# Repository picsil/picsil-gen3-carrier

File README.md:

# picsil-gen3-carrier
A carrier board for Particle Boron with support for three OneWire or dry contact sensors, onboard 32KB FRAM and DS18B20 temperature sensor, and ESD protected sensor inputs.

## NOTE
There are known problems with this circuit. Be aware of this before using it, since you will need to make changes.

### Known issues:
- J1-J3 use the wrong footprint. It uses STX-3120-3BM (mono), where it should be STX-3120-3B (stereo).
- U4 uses the wrong footprint, at least for the parts I have. I was unable to find a part that uses the footprint in this design.
- D4 is potentially a problem. Consider removing it if unsure.

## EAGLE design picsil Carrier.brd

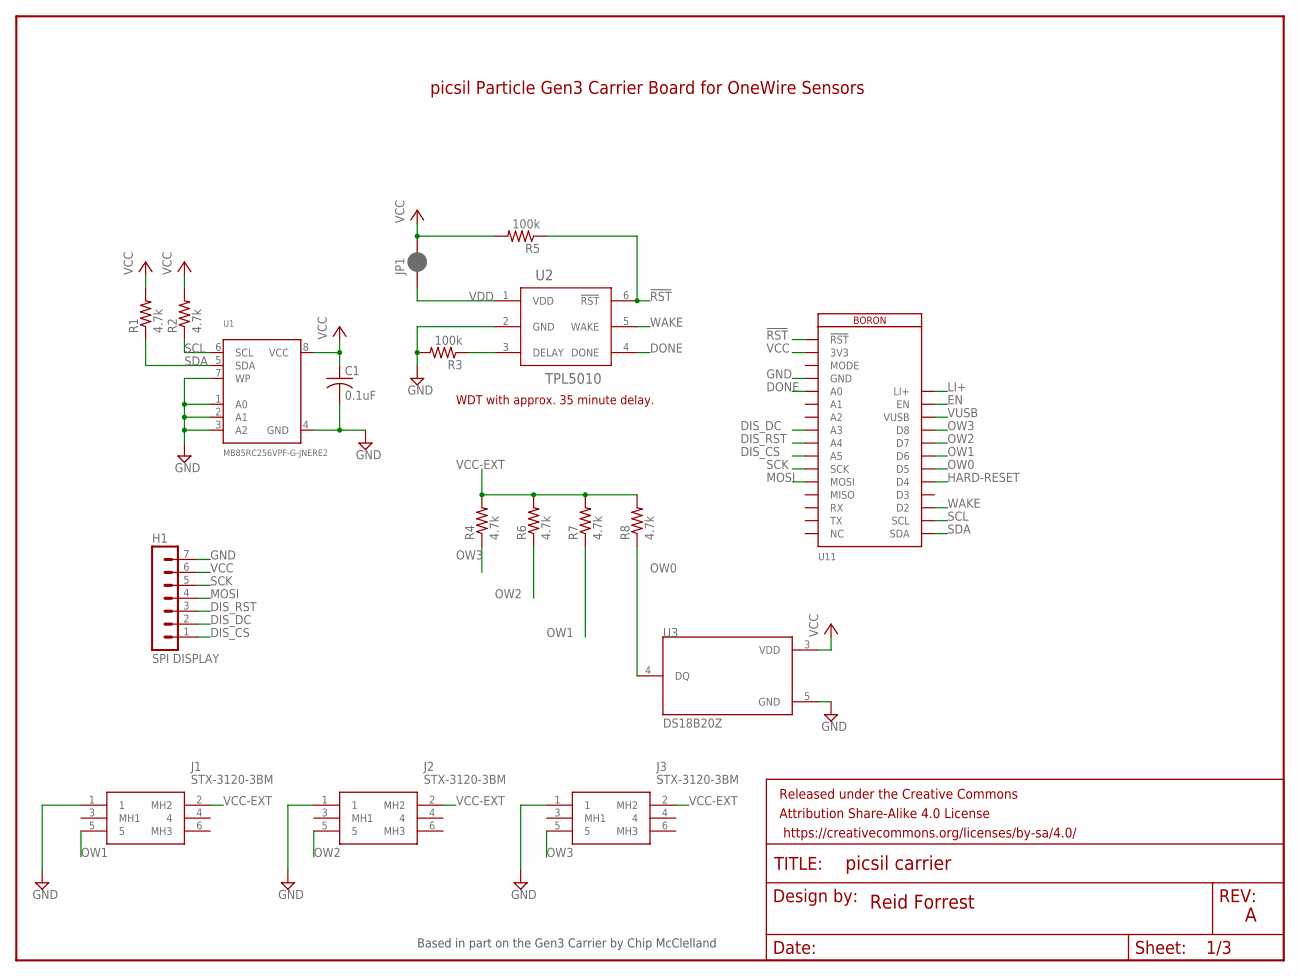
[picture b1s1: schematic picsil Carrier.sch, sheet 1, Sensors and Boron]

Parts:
C1: 0.1uF; C0805
FRAME1, FRAME4: FRAME-LETTER; CREATIVE_COMMONS
H1: SPI DISPLAY; MA07-1
J1, J2, J3: STX-3120-3BM; STX31203BM
JP1: JUMPER-SMT_2_NC_PASTE_SILK; SMT-JUMPER_2_NC_PASTE_SILK
R1, R2, R4, R6, R7, R8: 4.7k; R0805
R3, R5: 100k; R0805
U1: MB85RC256VPF-G-JNERE2; SOIC8_208MIL
U2: TPL5010; TSOT-23
U3: DS18B20Z; SOIC127P600X175-8N
U11: BORON

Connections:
!RST: R5.1, U2.6 (!RST), U11.1 (!RST)
DIS_CS: H1.1, U11.10 (A5)
DIS_DC: H1.2, U11.8 (A3)
DIS_RST: H1.3, U11.9 (A4)
DONE: U2.4 (DONE), U11.5 (A0)
EN: U11.27 (EN); also elsewhere on the board
GND: C1.2, H1.7, J1.1, J2.1, J3.1, R3.2, U1.1 (A0), U1.2 (A1), U1.3 (A2), U1.4 (GND), U1.7 (WP), U2.2 (GND), U3.5 (GND), U11.4 (GND); also elsewhere on the board
HARD-RESET: U11.21 (D4); also elsewhere on the board
LI+: U11.28 (LI+); also elsewhere on the board
MOSI: H1.4, U11.12 (MOSI)
unnamed: R3.1, U2.3 (DELAY)
OW0: R8.1, U3.4 (DQ), U11.22 (D5)
OW1: J1.5, R7.1, U11.23 (D6); also elsewhere on the board
OW2: J2.5, R6.1, U11.24 (D7); also elsewhere on the board
OW3: J3.5, R4.1, U11.25 (D8); also elsewhere on the board
SCK: H1.5, U11.11 (SCK)
SCL: R2.1, U1.6 (SCL), U11.18 (SCL)
SDA: R1.1, U1.5 (SDA), U11.17 (SDA)
VCC: C1.1, H1.6, JP1.2, R1.2, R2.2, R5.2, U1.8 (VCC), U3.3 (VDD), U11.2 (3V3); also elsewhere on the board
VCC-EXT: J1.2 (MH2), J2.2 (MH2), J3.2 (MH2), R4.2, R6.2, R7.2, R8.2; also elsewhere on the board
VDD: JP1.1, U2.1 (VDD)
VUSB: U11.26 (VUSB); also elsewhere on the board
WAKE: U2.5 (WAKE), U11.19 (D2)

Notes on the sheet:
WDT with approx. 35 minute delay.
picsil Particle Gen3 Carrier Board for OneWire Sensors
Reid Forrest
Based in part on the Gen3 Carrier by Chip McClelland

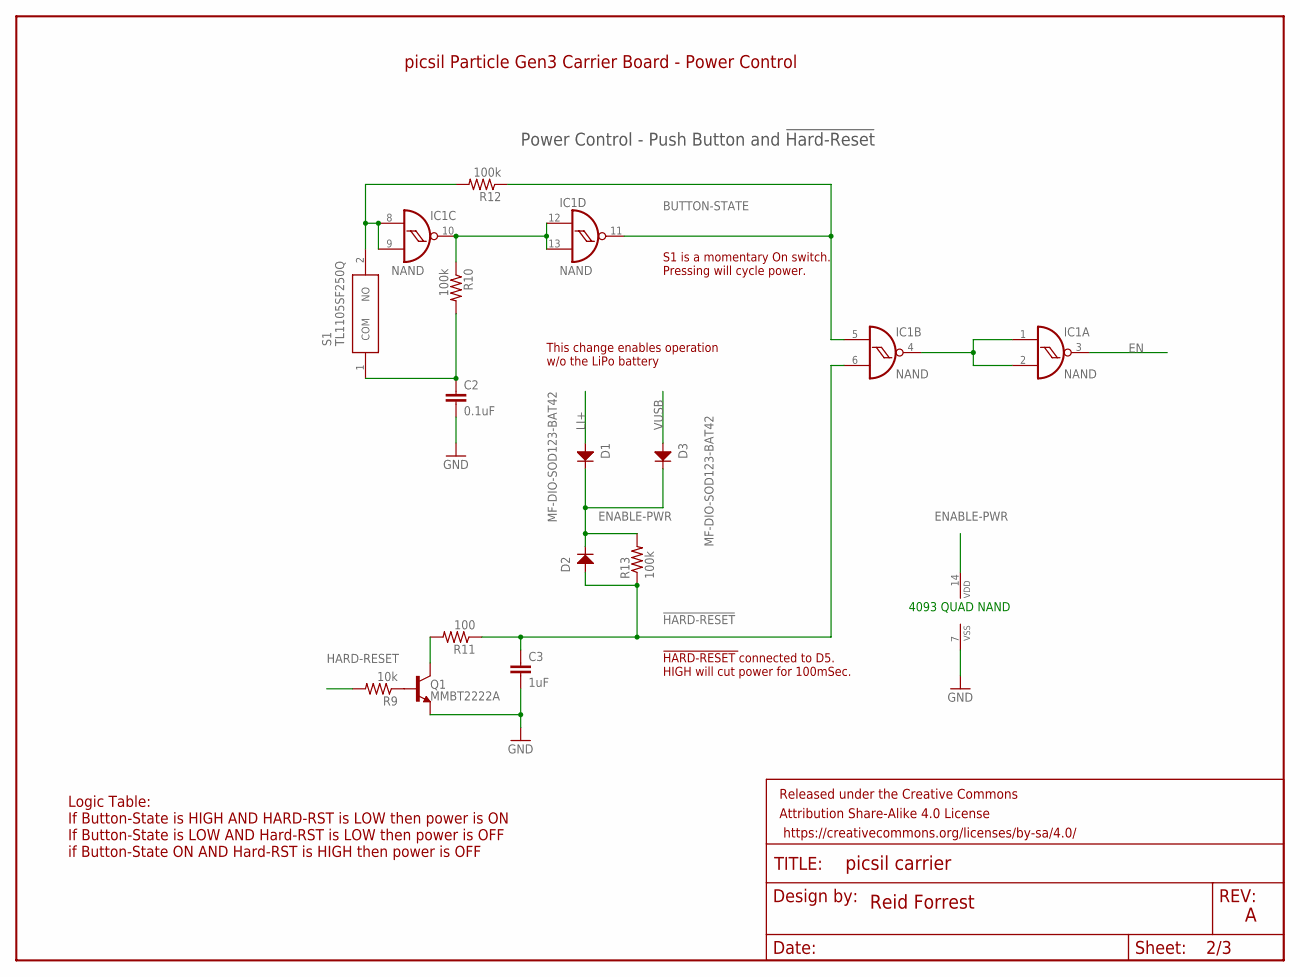
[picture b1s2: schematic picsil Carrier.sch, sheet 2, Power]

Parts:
C2: 0.1uF; 0805@1
C3: 1uF; 0805@1
D1, D2, D3: MF-DIO-SOD123-BAT42; SOD-123
FRAME2: FRAME-LETTER; CREATIVE_COMMONS
IC1: NAND; MC14093B-TSSOP14
Q1: MMBT2222A; SOT23-3
R9: 10k; 0805
R10, R12, R13: 100k; 0805
R11: 100; 0805
S1: TL1105SF250Q

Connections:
!HARD-RESET: C3.1, D2.ANODE, IC1.6 (I1), R11.1, R13.1
BUTTON-STATE: IC1.5 (I0), IC1.11 (O), R12.1
EN: IC1.3 (O); also elsewhere on the board
ENABLE-PWR: D1.CATHODE, D2.CATHODE, D3.CATHODE, IC1.14 (VDD), R13.2
GND: C2.2, C3.2, IC1.7 (VSS), Q1.2 (E); also elsewhere on the board
HARD-RESET: R9.2; also elsewhere on the board
LI+: D1.ANODE; also elsewhere on the board
unnamed: IC1.1 (I0), IC1.2 (I1), IC1.4 (O)
unnamed: IC1.10 (O), IC1.12 (I0), IC1.13 (I1), R10.1
unnamed: Q1.1 (B), R9.1
unnamed: Q1.3 (C), R11.2
unnamed: C2.1, R10.2, S1.1 (COM)
unnamed: IC1.8 (I0), IC1.9 (I1), R12.2, S1.2 (NO)
VUSB: D3.ANODE; also elsewhere on the board

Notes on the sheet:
4093 QUAD NAND
Power Control - Push Button and !Hard-Reset
Logic Table: If Button-State is HIGH AND HARD-RST is LOW then power is ON If Button-State is LOW AND Hard-RST is LOW then power is OFF if Button-State ON AND Hard-RST is HIGH then power is OFF
!HARD-RESET !connected to D5. HIGH will cut power for 100mSec.
S1 is a momentary On switch. Pressing will cycle power.
This change enables operation w/o the LiPo battery
picsil Particle Gen3 Carrier Board - Power Control
Reid Forrest

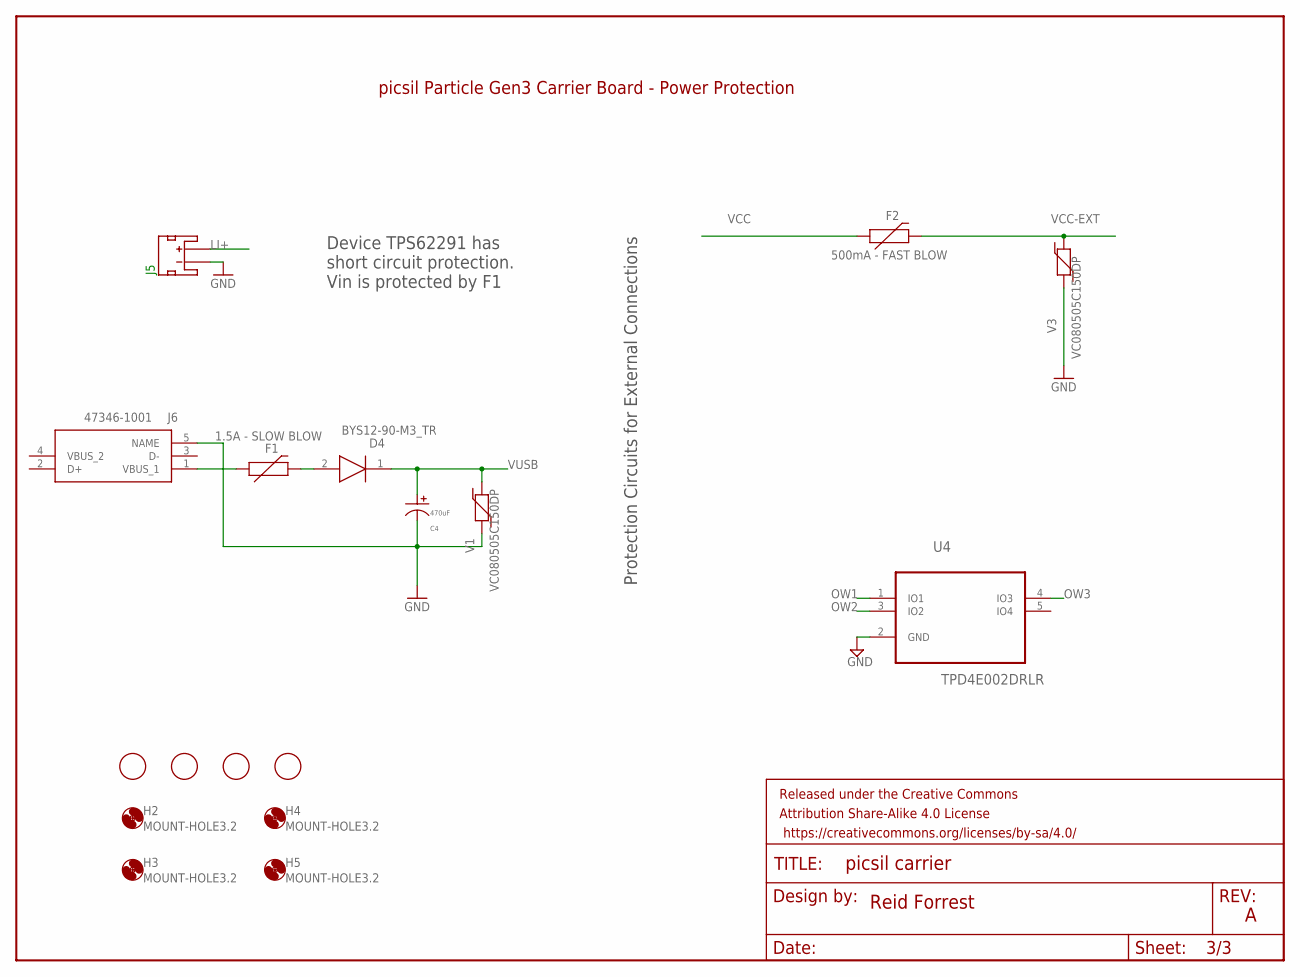
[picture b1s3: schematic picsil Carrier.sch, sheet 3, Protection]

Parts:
C4: 470uF; CP10MM
D4: BYS12-90-M3_TR; DIOM5127X229N
F1: 1.5A - SLOW BLOW; 1206
F2: 500mA - FAST BLOW; 1206
FRAME3: FRAME-LETTER; CREATIVE_COMMONS
H2, H3, H4, H5: MOUNT-HOLE3.2; 3,2
J5: S2B-PH-SM4-TB(LF)(SN); JST-2-SMD
J6: 47346-1001; 47346-0001
U4: TPD4E002DRLR; SOT50P280X60-5N
U$1, U$2, U$3, U$4: FIDUCIAL; FIDUCIAL_1MM
V1, V3: VC080505C150DP; 0805

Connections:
GND: C4.P$2, J5.1 (-), J6.5 (NAME), U4.2 (GND), V1.1, V3.1; also elsewhere on the board
LI+: J5.2 (+); also elsewhere on the board
unnamed: F1.1, J6.1 (VBUS_1)
unnamed: D4.2 (A), F1.2
OW1: U4.1 (IO1); also elsewhere on the board
OW2: U4.3 (IO2); also elsewhere on the board
OW3: U4.4 (IO3); also elsewhere on the board
VCC: F2.1; also elsewhere on the board
VCC-EXT: F2.2, V3.2; also elsewhere on the board
VUSB: C4.P$1, D4.1 (K), V1.2; also elsewhere on the board

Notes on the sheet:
Protection Circuits for External Connections
Device TPS62291 has short circuit protection. Vin is protected by F1
picsil Particle Gen3 Carrier Board - Power Protection
Reid Forrest

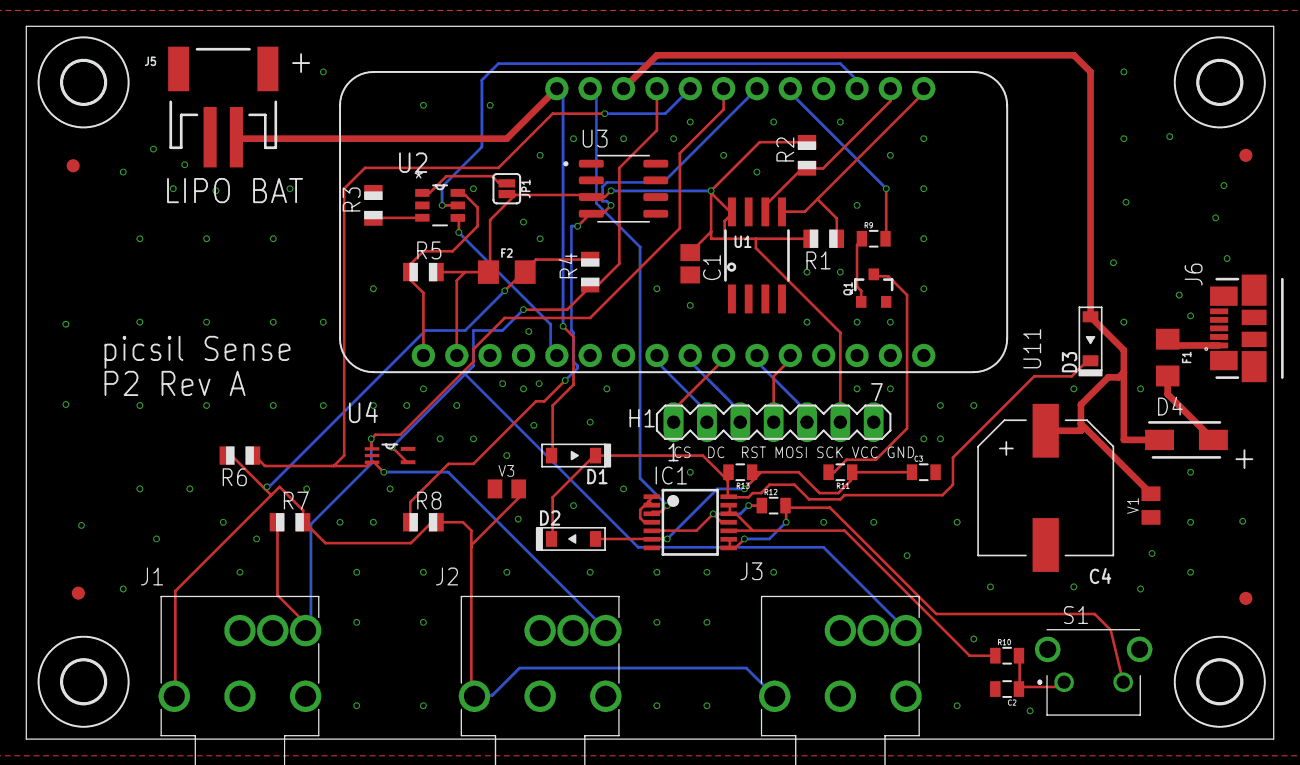
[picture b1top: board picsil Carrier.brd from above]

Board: 2 copper layers, 95.0 x 54.3 mm, 52 parts (0 on the bottom side), 34 nets.

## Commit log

2019-07-06 updated brd
2019-07-07 mounting holes and fiducials
2019-07-07 finalized Rev A
2019-07-07 remove boron mounting holes
2019-07-07 added vias around GND
2019-07-08 rerouted VCC to U1
2019-07-14 Rev A

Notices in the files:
parts and their libraries:
SparkFun-Capacitors: Licensing: CC v3.0 Share-Alike You are welcome to use this library for commercial purposes.
SparkFun-Fuses: Licensing: Creative Commons ShareAlike 4.0 International - https://creativecommons.org/licenses/by-sa/4.0
Particle-Devices: Licensing: Designed by Particle.
